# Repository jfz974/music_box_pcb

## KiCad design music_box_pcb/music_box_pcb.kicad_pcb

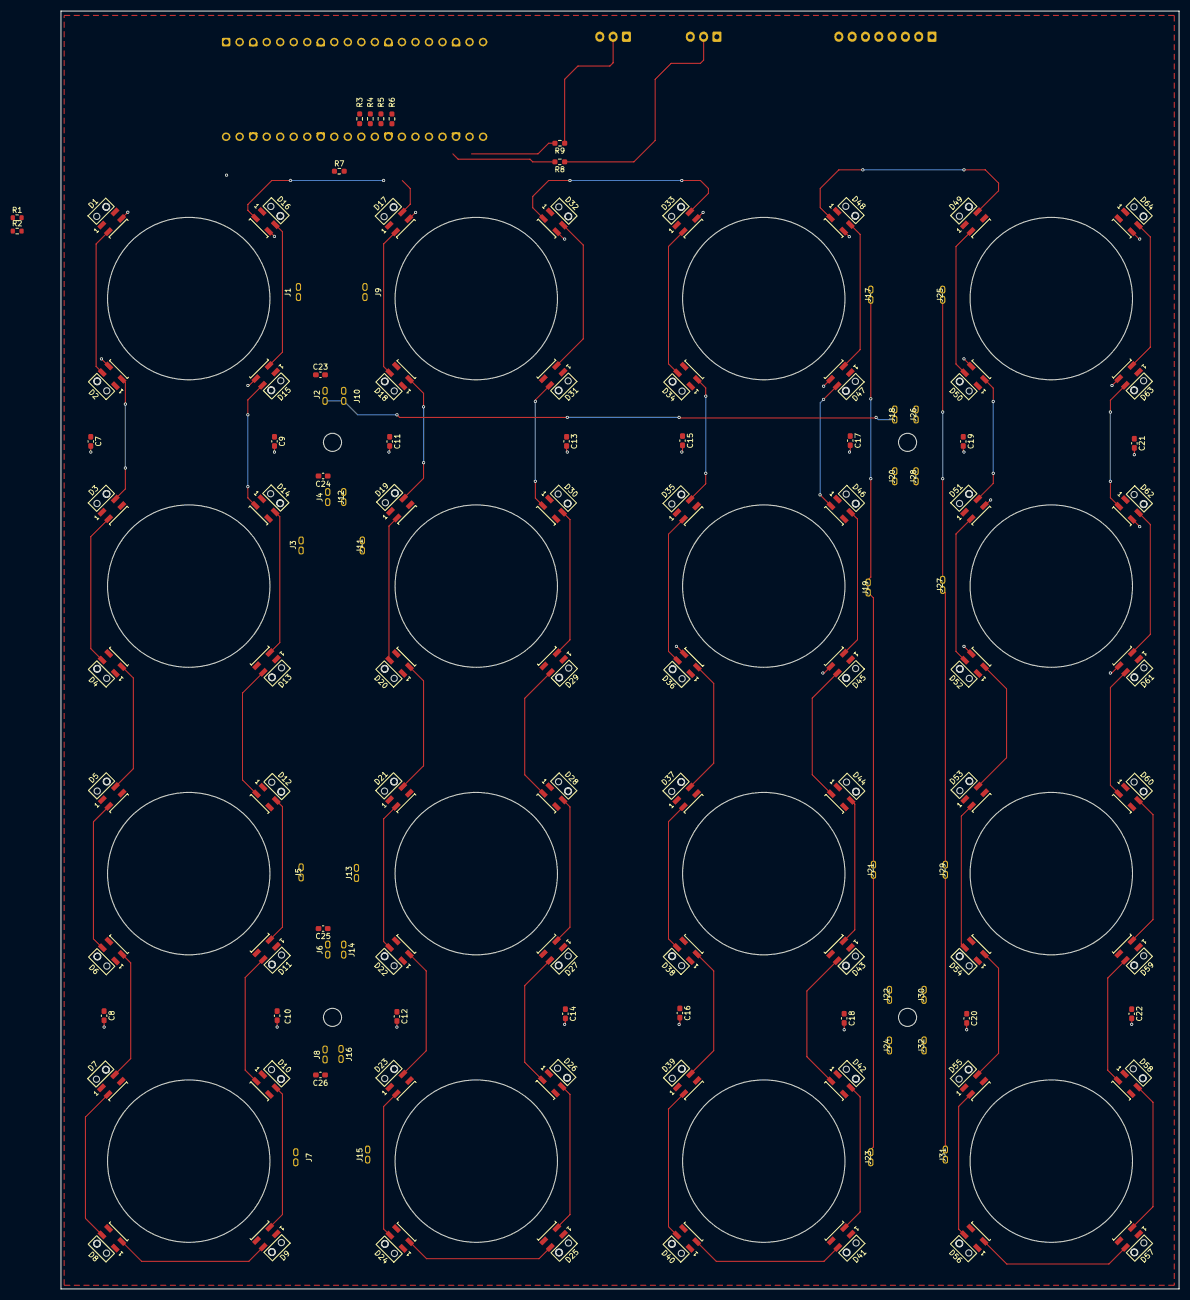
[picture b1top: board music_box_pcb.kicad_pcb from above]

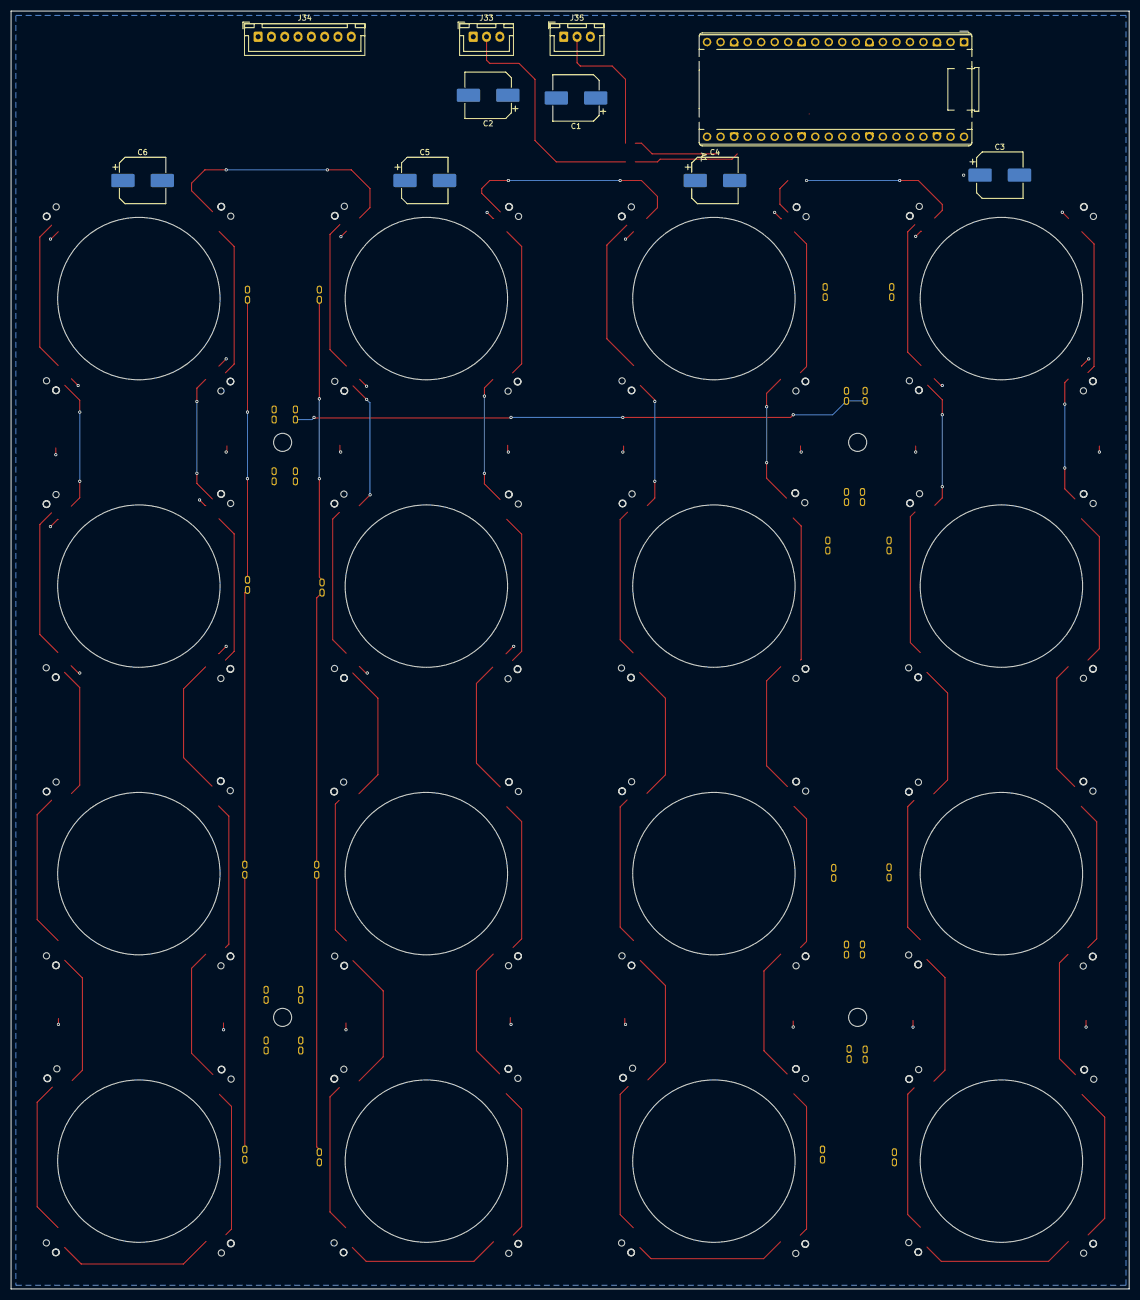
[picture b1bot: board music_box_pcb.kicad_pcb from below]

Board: 2 copper layers, 210.0 x 240.0 mm, 135 parts (10 on the bottom side), 80 nets.

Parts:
A1: RaspberryPi_Pico; RaspberryPi_Pico_Common_THT
C1, C2, C3, C4, C5, C6: 470µF, 16V; CP_Elec_8x10.5
C7, C8, C9, C10, C11, C12, C13, C14, C15, C16, C17, C18, C19, C20, C21, C22: 100nF; C_0603_1608Metric_Pad1.08x0.95mm_HandSolder
C23, C24, C25, C26: 100pF; C_0603_1608Metric_Pad1.08x0.95mm_HandSolder
D1, D2, D3, D4, D5, D6, D7, D8, D9, D10, D11, D12, D13, D14, D15, D16, D17, D18, D19, D20, D21, D22, D23, D24, D25, D26, D27, D28, D29, D30, D31, D32, D33, D34, D35, D36, D37, D38, D39, D40, D41, D42, D43, D44, D45, D46, D47, D48, D49, D50, D51, D52, D53, D54, D55, D56, D57, D58, D59, D60, D61, D62, D63, D64: WS2812B; LED_SK6812_3535_with_pipe
J1, J2, J3, J4, J5, J6, J7, J8, J9, J10, J11, J12, J13, J14, J15, J16, J17, J18, J19, J20, J21, J22, J23, J24, J25, J26, J27, J28, J29, J30, J31, J32: Conn_01x01_Pin; FASTON-2.8
J33, J35: Conn_01x03_Pin; JST_XH_B3B-XH-A_1x03_P2.50mm_Vertical
J34: Conn_01x08_Pin; JST_XH_B8B-XH-A_1x08_P2.50mm_Vertical
R1, R2: R; R_0603_1608Metric
R3, R4, R5, R6: 4.7k; R_0603_1608Metric_Pad0.98x0.95mm_HandSolder
R7, R8, R9: 330; R_0603_1608Metric_Pad0.98x0.95mm_HandSolder

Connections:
+3.3V: A1.36 (3V3), R3.1, R4.1, R5.1, R6.1
+5V: C1.1, C2.1, C3.1, C4.1, C5.1, C6.1, C7.1, C8.1, C9.1, C10.1, C11.1, C12.1, C13.1, C14.1, C15.1, C16.1, C17.1, C18.1, C19.1, C20.1, C21.1, C22.1, D1.1 (VDD), D2.1 (VDD), D3.1 (VDD), D4.1 (VDD), D5.1 (VDD), D6.1 (VDD), D7.1 (VDD), D8.1 (VDD), D9.1 (VDD), D10.1 (VDD), D11.1 (VDD), D12.1 (VDD), D13.1 (VDD), D14.1 (VDD), D15.1 (VDD), D16.1 (VDD), D17.1 (VDD), D18.1 (VDD), D19.1 (VDD), D20.1 (VDD), D21.1 (VDD), D22.1 (VDD), D23.1 (VDD), D24.1 (VDD), D25.1 (VDD), D26.1 (VDD), D27.1 (VDD), D28.1 (VDD), D29.1 (VDD), D30.1 (VDD), D31.1 (VDD), D32.1 (VDD), D33.1 (VDD), D34.1 (VDD), D35.1 (VDD), D36.1 (VDD), D37.1 (VDD), D38.1 (VDD), D39.1 (VDD), D40.1 (VDD), D41.1 (VDD), D42.1 (VDD), D43.1 (VDD), D44.1 (VDD), D45.1 (VDD), D46.1 (VDD), D47.1 (VDD), D48.1 (VDD), D49.1 (VDD), D50.1 (VDD), D51.1 (VDD), D52.1 (VDD), D53.1 (VDD), D54.1 (VDD), D55.1 (VDD), D56.1 (VDD), D57.1 (VDD), D58.1 (VDD), D59.1 (VDD), D60.1 (VDD), D61.1 (VDD), D62.1 (VDD), D63.1 (VDD), D64.1 (VDD), J33.1, J34.1, J34.3, J34.5, J34.7, J35.1
GND: A1.3 (GND), A1.8 (GND), A1.13 (GND), A1.18 (GND), A1.23 (GND), A1.28 (GND), A1.33 (AGND), A1.38 (GND), C1.2, C2.2, C3.2, C4.2, C5.2, C6.2, C7.2, C8.2, C9.2, C10.2, C11.2, C12.2, C13.2, C14.2, C15.2, C16.2, C17.2, C18.2, C19.2, C20.2, C21.2, C22.2, C23.2, C24.2, C25.2, C26.2, D1.3 (VSS), D2.3 (VSS), D3.3 (VSS), D4.3 (VSS), D5.3 (VSS), D6.3 (VSS), D7.3 (VSS), D8.3 (VSS), D9.3 (VSS), D10.3 (VSS), D11.3 (VSS), D12.3 (VSS), D13.3 (VSS), D14.3 (VSS), D15.3 (VSS), D16.3 (VSS), D17.3 (VSS), D18.3 (VSS), D19.3 (VSS), D20.3 (VSS), D21.3 (VSS), D22.3 (VSS), D23.3 (VSS), D24.3 (VSS), D25.3 (VSS), D26.3 (VSS), D27.3 (VSS), D28.3 (VSS), D29.3 (VSS), D30.3 (VSS), D31.3 (VSS), D32.3 (VSS), D33.3 (VSS), D34.3 (VSS), D35.3 (VSS), D36.3 (VSS), D37.3 (VSS), D38.3 (VSS), D39.3 (VSS), D40.3 (VSS), D41.3 (VSS), D42.3 (VSS), D43.3 (VSS), D44.3 (VSS), D45.3 (VSS), D46.3 (VSS), D47.3 (VSS), D48.3 (VSS), D49.3 (VSS), D50.3 (VSS), D51.3 (VSS), D52.3 (VSS), D53.3 (VSS), D54.3 (VSS), D55.3 (VSS), D56.3 (VSS), D57.3 (VSS), D58.3 (VSS), D59.3 (VSS), D60.3 (VSS), D61.3 (VSS), D62.3 (VSS), D63.3 (VSS), D64.3 (VSS), J33.3, J34.2, J34.4, J34.6, J34.8, J35.3
LED_CTRL: D1.4 (DIN), R7.1
unnamed: A1.14 (GPIO10), R7.2
unnamed: A1.15 (GPIO11), R8.2
unnamed: A1.16 (GPIO12), R9.2
unnamed: D1.2 (DOUT), D2.4 (DIN)
unnamed: D2.2 (DOUT), D3.4 (DIN)
unnamed: D3.2 (DOUT), D4.4 (DIN)
unnamed: D4.2 (DOUT), D5.4 (DIN)
unnamed: D5.2 (DOUT), D6.4 (DIN)
unnamed: D6.2 (DOUT), D7.4 (DIN)
unnamed: D7.2 (DOUT), D8.4 (DIN)
unnamed: D8.2 (DOUT), D9.4 (DIN)
unnamed: D9.2 (DOUT), D10.4 (DIN)
unnamed: D10.2 (DOUT), D11.4 (DIN)
unnamed: D11.2 (DOUT), D12.4 (DIN)
unnamed: D12.2 (DOUT), D13.4 (DIN)
unnamed: D13.2 (DOUT), D14.4 (DIN)
unnamed: D14.2 (DOUT), D15.4 (DIN)
unnamed: D15.2 (DOUT), D16.4 (DIN)
unnamed: D16.2 (DOUT), D17.4 (DIN)
unnamed: D17.2 (DOUT), D18.4 (DIN)
unnamed: D18.2 (DOUT), D19.4 (DIN)
unnamed: D19.2 (DOUT), D20.4 (DIN)
unnamed: D20.2 (DOUT), D21.4 (DIN)
unnamed: D21.2 (DOUT), D22.4 (DIN)
unnamed: D22.2 (DOUT), D23.4 (DIN)
unnamed: D23.2 (DOUT), D24.4 (DIN)
unnamed: D24.2 (DOUT), D25.4 (DIN)
unnamed: D25.2 (DOUT), D26.4 (DIN)
unnamed: D26.2 (DOUT), D27.4 (DIN)
unnamed: D27.2 (DOUT), D28.4 (DIN)
unnamed: D28.2 (DOUT), D29.4 (DIN)
unnamed: D29.2 (DOUT), D30.4 (DIN)
unnamed: D30.2 (DOUT), D31.4 (DIN)
unnamed: D31.2 (DOUT), D32.4 (DIN)
unnamed: D32.2 (DOUT), D33.4 (DIN)
unnamed: D33.2 (DOUT), D34.4 (DIN)
unnamed: D34.2 (DOUT), D35.4 (DIN)
unnamed: D35.2 (DOUT), D36.4 (DIN)
unnamed: D36.2 (DOUT), D37.4 (DIN)
unnamed: D37.2 (DOUT), D38.4 (DIN)
unnamed: D38.2 (DOUT), D39.4 (DIN)
unnamed: D39.2 (DOUT), D40.4 (DIN)
unnamed: D40.2 (DOUT), D41.4 (DIN)
unnamed: D41.2 (DOUT), D42.4 (DIN)
unnamed: D42.2 (DOUT), D43.4 (DIN)
unnamed: D43.2 (DOUT), D44.4 (DIN)
unnamed: D44.2 (DOUT), D45.4 (DIN)
unnamed: D45.2 (DOUT), D46.4 (DIN)
unnamed: D46.2 (DOUT), D47.4 (DIN)
unnamed: D47.2 (DOUT), D48.4 (DIN)
unnamed: D48.2 (DOUT), D49.4 (DIN)
unnamed: D49.2 (DOUT), D50.4 (DIN)
unnamed: D50.2 (DOUT), D51.4 (DIN)
unnamed: D51.2 (DOUT), D52.4 (DIN)
unnamed: D52.2 (DOUT), D53.4 (DIN)
unnamed: D53.2 (DOUT), D54.4 (DIN)
unnamed: D54.2 (DOUT), D55.4 (DIN)
unnamed: D55.2 (DOUT), D56.4 (DIN)
unnamed: D56.2 (DOUT), D57.4 (DIN)
unnamed: D57.2 (DOUT), D58.4 (DIN)
unnamed: D58.2 (DOUT), D59.4 (DIN)
unnamed: D59.2 (DOUT), D60.4 (DIN)
unnamed: D60.2 (DOUT), D61.4 (DIN)
unnamed: D61.2 (DOUT), D62.4 (DIN)
unnamed: D62.2 (DOUT), D63.4 (DIN)
unnamed: D63.2 (DOUT), D64.4 (DIN)
STRIP_1: J33.2, R8.1
STRIP_2: J35.2, R9.1
SW_C1: A1.4 (GPIO2), J1.1 (Pin_1_1), J3.1 (Pin_1_1), J5.1 (Pin_1_1), J7.1 (Pin_1_1)
SW_C2: A1.5 (GPIO3), J9.1 (Pin_1_1), J11.1 (Pin_1_1), J13.1 (Pin_1_1), J15.1 (Pin_1_1)
SW_C3: A1.6 (GPIO4), J17.1 (Pin_1_1), J19.1 (Pin_1_1), J21.1 (Pin_1_1), J23.1 (Pin_1_1)
SW_C4: A1.7 (GPIO5), J25.1 (Pin_1_1), J27.1 (Pin_1_1), J29.1 (Pin_1_1), J31.1 (Pin_1_1)
SW_L1: A1.9 (GPIO6), C23.1, J2.1 (Pin_1_1), J10.1 (Pin_1_1), J18.1 (Pin_1_1), J26.1 (Pin_1_1), R3.2
SW_L2: A1.10 (GPIO7), C24.1, J4.1 (Pin_1_1), J12.1 (Pin_1_1), J20.1 (Pin_1_1), J28.1 (Pin_1_1), R4.2
SW_L3: A1.11 (GPIO8), C25.1, J6.1 (Pin_1_1), J14.1 (Pin_1_1), J22.1 (Pin_1_1), J30.1 (Pin_1_1), R5.2
SW_L4: A1.12 (GPIO9), C26.1, J8.1 (Pin_1_1), J16.1 (Pin_1_1), J24.1 (Pin_1_1), J32.1 (Pin_1_1), R6.2
